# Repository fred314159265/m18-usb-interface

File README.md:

# M18 USB Interface

A USB-C board that plugs into a Milwaukee M18 battery so a PC can talk to the pack's diagnostic pins.

Revision v1.0. The M18 connector is on the back of the board.

## Companion software

Read a health report, cell data, and charge history with [m18-protocol-rs](https://github.com/fred314159265/m18-protocol-rs):

```bash
cargo run --example health_report -- COM3
```

On Linux or macOS, pass the serial device instead, for example `/dev/ttyUSB0`.

The protocol comes from the reverse engineering in [mnh-jansson/m18-protocol](https://github.com/mnh-jansson/m18-protocol). That Python tool works with this board as well.

## Features

- USB-C and an FT234XD serial bridge, with RX and TX LEDs.
- Two LTV-817S optocouplers. The battery UART is on its own ground, separate from the PC.
- J2 is driven as a roughly 0–12 V signal, which is what the pack expects. J1 comes back from the pack at about 3.3–5 V.
- ESD diodes on the exposed battery pins.
- Everything except the M18 connector is chosen from the JLCPCB assembly library. Solder the connector on afterwards.
- KiCad 9 sources. The v1.0 fabrication package is in the repo and on the [v1.0 release](https://github.com/fred314159265/m18-usb-interface/releases/tag/v1.0).

## Battery pins

These photos are from the [Tool Scientist](https://www.youtube.com/watch?v=tHj0-Gzvbeo) video and the [m18-protocol hardware notes](https://github.com/mnh-jansson/m18-protocol#hardware). They show the pack terminals this board connects to.

| Pin | Role | Level |
| --- | --- | --- |
| B+ | Pack positive | About 12.5–21 V |
| J1 | Output from the pack | About 3.3–5 V |
| C | Charge terminal | |
| J2 | Input to the pack | About 0–12 V |
| B− | Pack negative | |

`Images/wiring.png` is the discrete FTDI adapter and level shifter that this PCB replaces.

## One-time FTDI setup

The optocouplers invert TX and RX. Program the FT234XD once with [FT_Prog](https://ftdichip.com/utilities/#ft_prog), or the link will not decode.

Template: [`m18-usb-interface-pcb/Releases/v1.0/M18_Interface_FT_Prog_Template.xml`](m18-usb-interface-pcb/Releases/v1.0/M18_Interface_FT_Prog_Template.xml)

1. Install FT_Prog.
2. Choose `File → Open Template…` and select the template.
3. Plug in the board. Choose `Devices → Scan and Parse`.
4. Right-click the device, choose `Apply Template`, and select the template.
5. Choose `Devices → Program`.

The template writes:

- USB product name `M18 USB Interface`
- TX and RX inverted
- the VCP driver, so the board shows up as a normal COM port
- 8 mA drive, slow slew, and Schmitt trigger inputs

## Build

Fabrication files for v1.0:

- [Release v1.0](https://github.com/fred314159265/m18-usb-interface/releases/tag/v1.0), with the gerber zip, schematic PDF, and FT_Prog template attached
- Gerbers and assembly files in [`m18-usb-interface-pcb/Releases/v1.0/production/`](m18-usb-interface-pcb/Releases/v1.0/production)
- [Schematic PDF](m18-usb-interface-pcb/Releases/v1.0/m18-usb-interface-pcb_v1.0.pdf)
- [Interactive BOM](https://fred314159265.github.io/m18-usb-interface/m18-usb-interface-pcb/bom/ibom.html)

1. Order the board from the production zip. It includes the gerbers, BOM, and pick-and-place file.
2. Solder on an M18 battery connector. The footprint matches common shells such as [this one](https://www.aliexpress.com/item/1005009824719494.html).
3. Program the FTDI chip with the template above.
4. Plug the board into an M18 pack, and plug USB-C into the PC.
5. Run `health_report` from [m18-protocol-rs](https://github.com/fred314159265/m18-protocol-rs).

## Safety

This is not a Milwaukee Tool product, and Milwaukee has not endorsed it. Lithium-ion packs can burn if they are shorted or wired wrong. Isolation on this board is not a guarantee if it is assembled incorrectly. Use it at your own risk.

## License

Public domain under [The Unlicense](LICENSE).

## Thanks

[Tool Scientist](https://youtu.be/tHj0-Gzvbeo) and the contributors to [m18-protocol](https://github.com/mnh-jansson/m18-protocol) documented the pins and the protocol this board is built for.

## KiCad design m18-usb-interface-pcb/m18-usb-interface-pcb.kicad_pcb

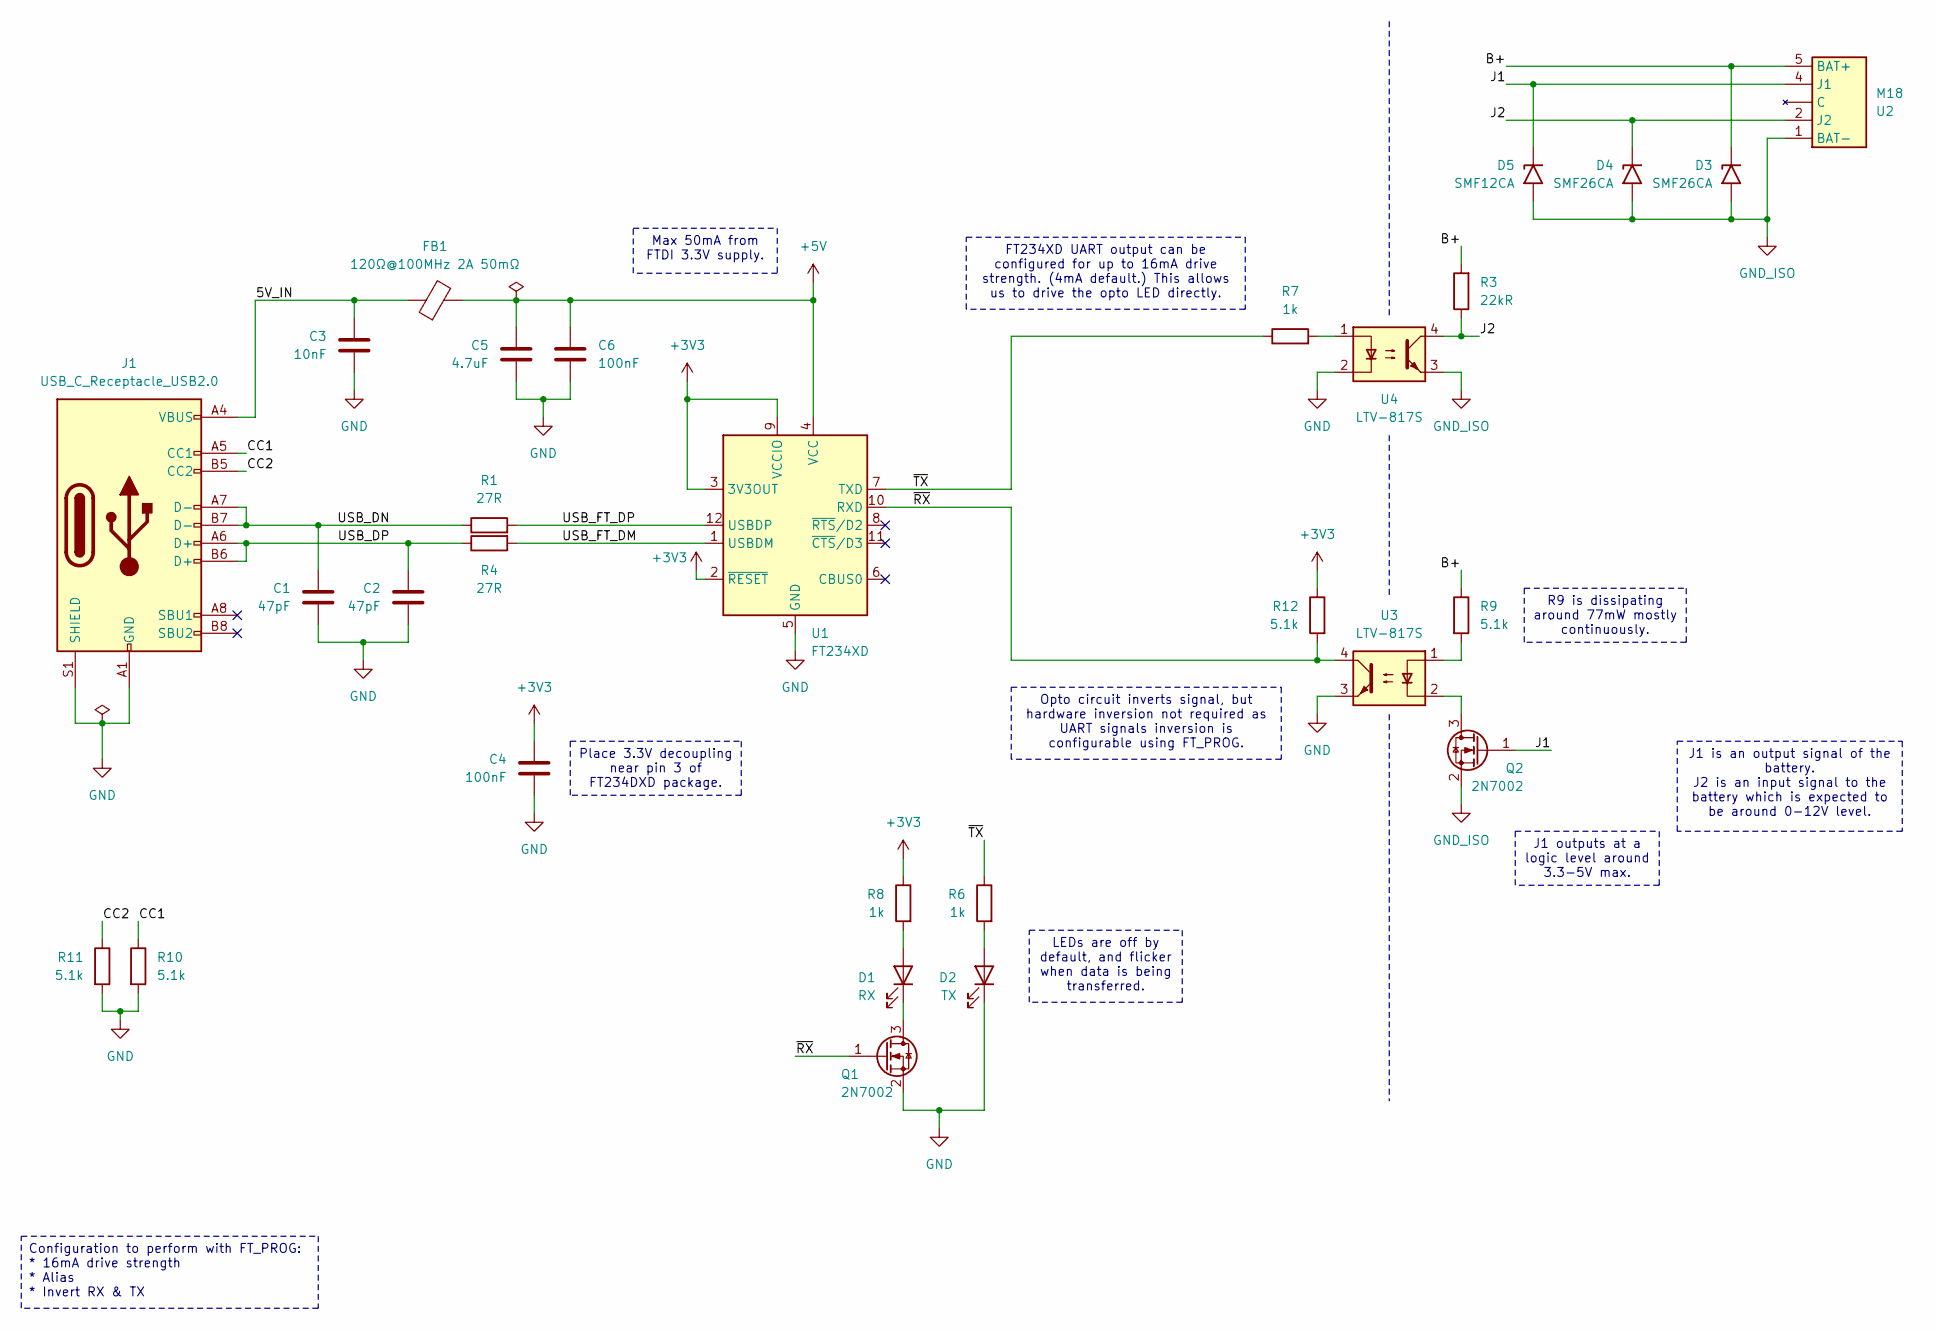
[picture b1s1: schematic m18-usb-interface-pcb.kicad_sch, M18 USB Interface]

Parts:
C1, C2: 47pF; C_0603_1608Metric; Manufacturer Part # CL10C470JB8NNNC; LCSC Part # C1671
C3: 10nF; C_0603_1608Metric; Manufacturer Part # 0603B103K500NT; LCSC Part # C57112
C4, C6: 100nF; C_0603_1608Metric; Manufacturer Part # CC0603KRX7R9BB104; LCSC Part # C14663
C5: 4.7uF; C_0603_1608Metric; Manufacturer Part # CL10A475KO8NNNC; LCSC Part # C19666
D1: RX; LED_0603_1608Metric; Manufacturer Part # KT-0603R; LCSC Part # C2286
D2: TX; LED_0603_1608Metric; Manufacturer Part # KT-0603R; LCSC Part # C2286
D3, D4: SMF26CA; D_SOD-123F; Manufacturer Part # SMF26CA; LCSC Part # C19077516
D5: SMF12CA; D_SOD-123F; Manufacturer Part # SMF12CA; LCSC Part # C19077507
FB1: 120Ω@100MHz 2A 50mΩ; L_0603_1608Metric; Manufacturer Part # BLM18PG121SN1D; LCSC Part # C14709
J1: USB_C_Receptacle_USB2.0; USB_C_Receptacle_XKB_U262-16XN-4BVC11; Manufacturer Part # U262-161N-4BVC11; LCSC Part # C319148
Q1, Q2: 2N7002; SOT-23; Manufacturer Part # 2N7002; LCSC Part # C8545
R1, R4: 27R; R_0603_1608Metric; Manufacturer Part # 0603WAF270JT5E; LCSC Part # C25190
R3: 22kR; R_0603_1608Metric; Manufacturer Part # 0603WAF2202T5E; LCSC Part # C31850
R6, R7, R8: 1k; R_0603_1608Metric; Manufacturer Part # 0603WAF1000T5E; LCSC Part # C22775
R9, R10, R11, R12: 5.1k; R_0603_1608Metric; Manufacturer Part # 0603WAF5101T5E; LCSC Part # C23186
U1: FT234XD; WDFN-12-1EP_3x3mm_P0.45mm_EP1.7x2.5mm; Manufacturer Part # FT234XD-R; LCSC Part # C132158
U2: M18; M18_Battery_Interface
U3, U4: LTV-817S; SMDIP-4_W9.53mm; Manufacturer Part # LTV-817S-TA1-C; LCSC Part # C109227

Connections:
+3V3: C4.1, R8.1, R12.1, U1.2 (~RESET), U1.3 (3V3OUT), U1.9 (VCCIO)
+5V: C5.1, C6.1, FB1.2, U1.4 (VCC)
/5V_IN: C3.1, FB1.1, J1.A4 (VBUS), J1.A9 (VBUS), J1.B4 (VBUS), J1.B9 (VBUS)
/B+: D3.1 (A1), R3.2, R9.1, U2.5 (BAT+)
/CC1: J1.A5 (CC1), R10.1
/CC2: J1.B5 (CC2), R11.1
/J1: D5.1 (A1), Q2.1 (G), U2.4 (J1)
/J2: D4.1 (A1), R3.1, U2.2 (J2), U4.4
/USB_DN: C1.1, J1.A7 (D-), J1.B7 (D-), R1.1
/USB_DP: C2.1, J1.A6 (D+), J1.B6 (D+), R4.1
/USB_FT_DM: R4.2, U1.1 (USBDM)
/USB_FT_DP: R1.2, U1.12 (USBDP)
/~RX: Q1.1 (G), R12.2, U1.10 (RXD), U3.4
/~TX: R6.1, R7.1, U1.7 (TXD)
GND: C1.2, C2.2, C3.2, C4.2, C5.2, C6.2, D2.1 (K), J1.A1 (GND), J1.A12 (GND), J1.B1 (GND), J1.B12 (GND), J1.S1 (SHIELD), Q1.2 (S), R10.2, R11.2, U1.5 (GND), U1.13 (GND), U3.3, U4.2
GND_ISO: D3.2 (A2), D4.2 (A2), D5.2 (A2), Q2.2 (S), U2.1 (BAT-), U4.3
unnamed: D1.2 (A), R8.2
unnamed: D1.1 (K), Q1.3 (D)
unnamed: D2.2 (A), R6.2
unnamed: Q2.3 (D), U3.2
unnamed: R7.2, U4.1
unnamed: R9.2, U3.1

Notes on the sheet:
Max 50mA from FTDI 3.3V supply.
LEDs are off by default, and flicker when data is being transferred.
J1 is an output signal of the battery. J2 is an input signal to the battery which is expected to be around 0-12V level.
R9 is dissipating around 77mW mostly continuously.
Place 3.3V decoupling near pin 3 of FT234DXD package.
Opto circuit inverts signal, but hardware inversion not required as UART signals inversion is configurable using FT_PROG.
FT234XD UART output can be configured for up to 16mA drive strength. (4mA default.) This allows us to drive the opto LED directly.
J1 outputs at a logic level around 3.3-5V max.
Configuration to perform with FT_PROG: * 16mA drive strength * Alias * Invert RX & TX

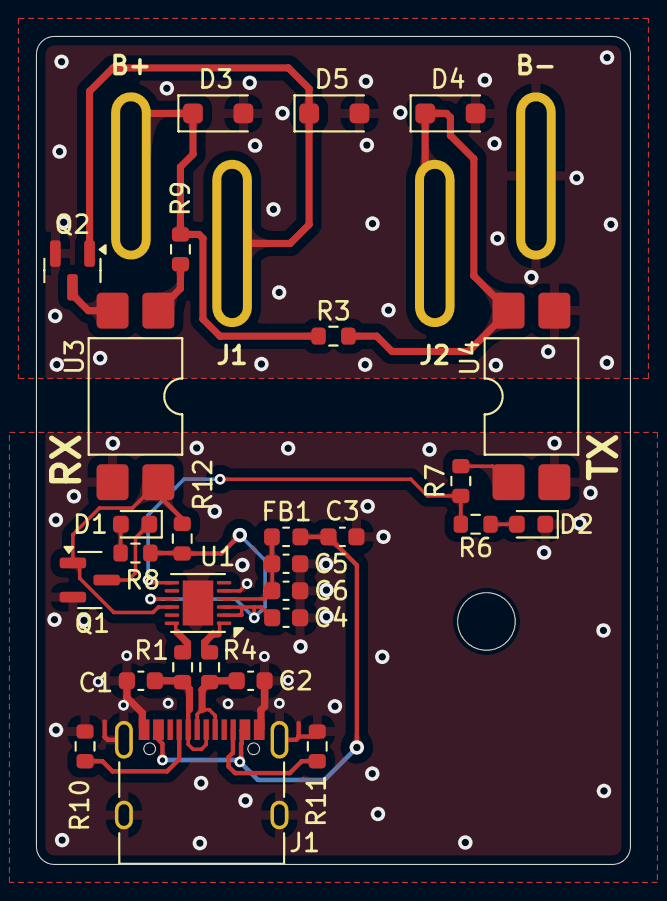
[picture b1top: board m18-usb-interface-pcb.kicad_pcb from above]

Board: 2 copper layers, 33.0 x 46.0 mm, 29 parts (1 on the bottom side), 22 nets.

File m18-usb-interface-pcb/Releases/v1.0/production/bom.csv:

Designator,Footprint,Quantity,Value,LCSC Part #
"C1, C2",0603,2,47pF,C1671
C3,0603,1,10nF,C57112
"C4, C6",0603,2,100nF,C14663
C5,0603,1,4.7uF,C19666
D1,0603,1,RX,C2286
D2,0603,1,TX,C2286
"D3, D4",D_SOD-123F,2,SMF26CA,C19077516
D5,D_SOD-123F,1,SMF12CA,C19077507
FB1,0603,1,120Ω@100MHz 2A 50mΩ,C14709
J1,USB_C_Receptacle_XKB_U262-16XN-4BVC11,1,USB_C_Receptacle_USB2.0,C319148
"Q1, Q2",SOT-23,2,2N7002,C8545
"R1, R4",0603,2,27R,C25190
"R10, R11, R12, R9",0603,4,5.1k,C23186
R3,0603,1,22kR,C31850
"R6, R7, R8",0603,3,1k,C22775
U1,WDFN-12-1EP_3x3mm_P0.45mm_EP1.7x2.5mm,1,FT234XD,C132158
U2,M18_Battery_Interface,1,M18,
"U3, U4",SMDIP-4_W9.53mm,2,LTV-817S,C109227

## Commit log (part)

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2025-09-17 v1.0 PCB released
2025-10-19 Added template file for programming FTDI setting w/ FT_Prog.
    Tracked some production outputs which were missed.
